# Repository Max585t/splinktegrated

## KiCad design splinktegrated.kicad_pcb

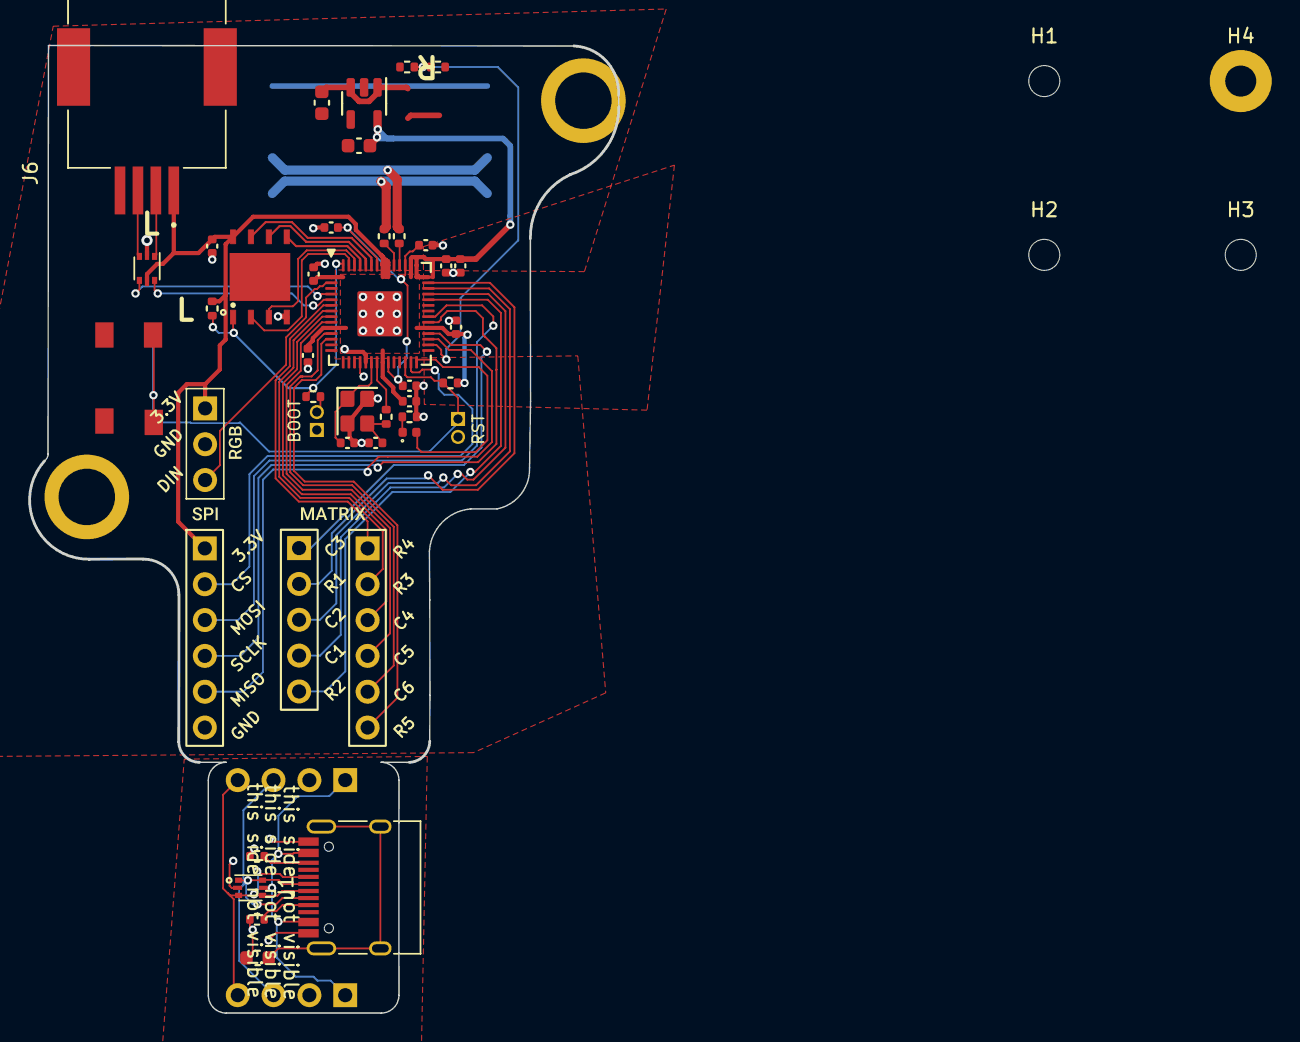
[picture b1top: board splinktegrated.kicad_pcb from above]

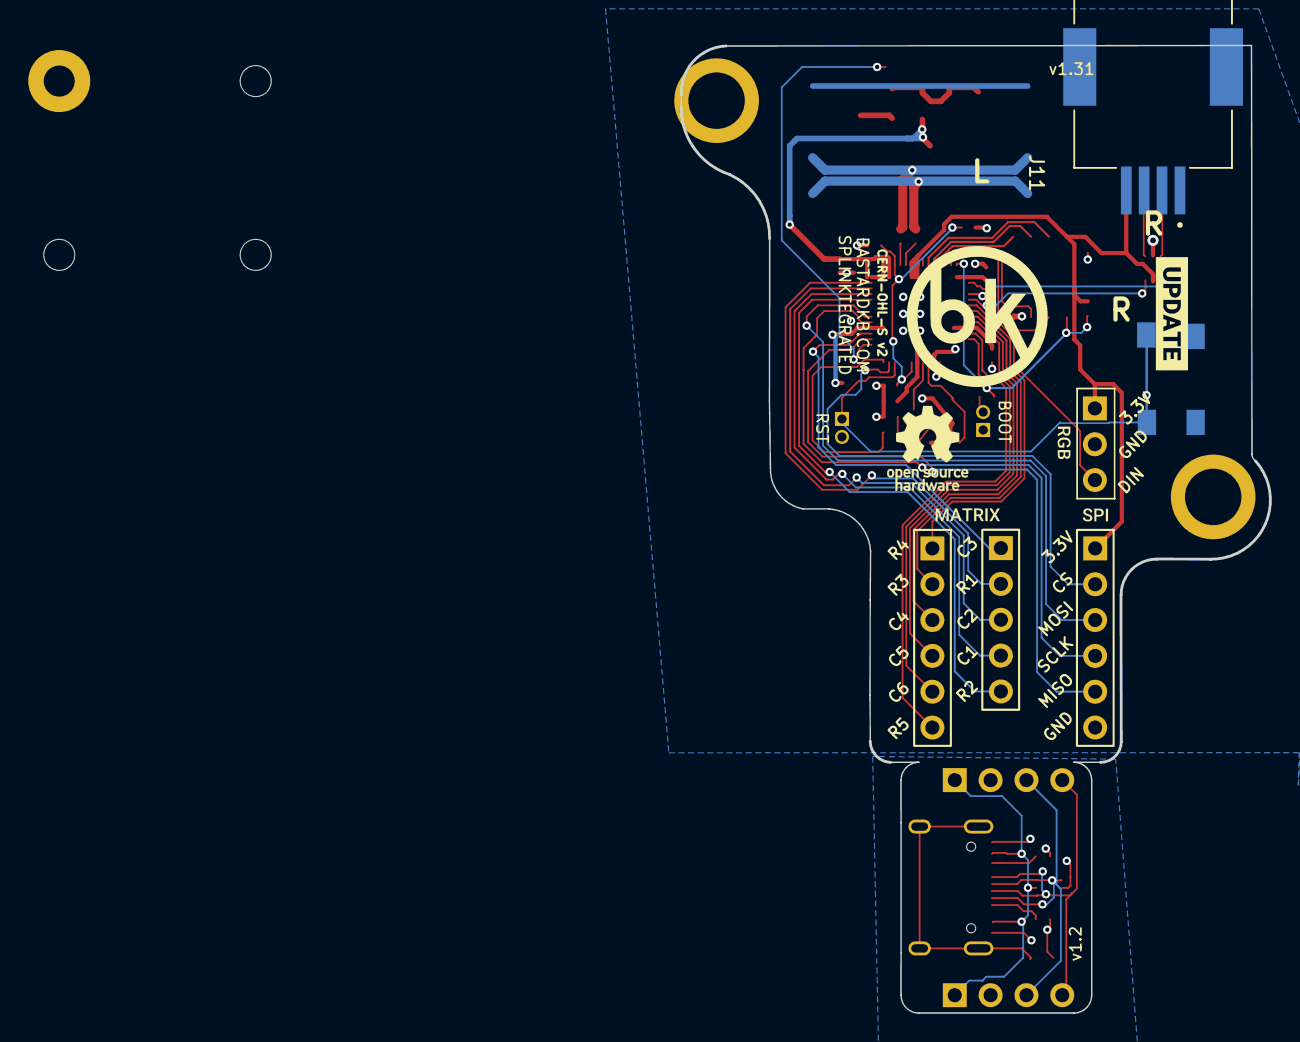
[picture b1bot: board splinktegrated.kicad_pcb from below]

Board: 2 copper layers, 41.8 x 68.6 mm, 58 parts (6 on the bottom side), 47 nets.

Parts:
C1, C2: 1µ; C_0603_1608Metric
C3, C4: 15p; C_0402_1005Metric
C5, C6: 1µ; C_0402_1005Metric
C7, C8, C9, C10, C11, C12, C13, C14: 100n; C_0402_1005Metric
D1: LED; LED_0402_1005Metric
FB1: FerriteBead_Small; L_0603_1608Metric
H1, H2, H3: MountingHole; MountingHole_2.2mm_M2
H4: MountingHole_Pad; MountingHole_2.2mm_M2_Pad
J1: USB_C_Receptacle_USB2.0; USB_C_Receptacle_HRO_TYPE-C-31-M-12
J2, J3: Conn_01x04_Female; PinHeader_1x04_P2.54mm_Vertical
J5: Conn_01x02; PinHeader_1x02_P1.27mm_Vertical
J6, J11: RJ9; AMPHENOL_73306-111LF
J7: trackball; 6_PinHeader
J8: Ribbon; 6_PinHeader
J9: RGB; header1x03
J10: Ribbon; 5_PinHeader
J13: Conn_01x02_Female; PinHeader_1x02_P1.27mm_Vertical
R1, R3, R8: 1k; R_0402_1005Metric
R2, R9, R11: 10k; R_0402_1005Metric
R4, R5, R10: 5.1k; R_0402_1005Metric
R6, R7: 27; R_0402_1005Metric
SW1, SW2: SW_SPST; PushSwitch
U1: RP2040; QFN-56-1EP_7x7mm_P0.4mm_EP3.2x3.2mm
U2, U4: USBLC6-2P6; SOT-666
U3: XC6210B332MR-G; SOT-23-5
U5: W25Q128JVS; W25Q128JVPIQ
Y1: Crystal_GND24; Crystal_SMD_2520-4Pin_2.5x2.0mm
kibuzzard-61F01C84, kibuzzard-61F01C84#2: G***; kibuzzard-61F01C84
kibuzzard-61F019CB, kibuzzard-61F019CB#2: G***; kibuzzard-61F019CB
kibuzzard-61F01940, kibuzzard-61F01940#2: G***; kibuzzard-61F01940
kibuzzard-61F01957, kibuzzard-61F01957#2: G***; kibuzzard-61F01957

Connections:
+1V1: C6.1, C7.1, C8.1, U1.23 (DVDD), U1.45 (VREG_VOUT), U1.50 (DVDD)
+3V3: C2.1, C5.1, C9.1, C10.1, C11.1, C12.1, C13.1, C14.1, J6.1, J7.1, J9.1, J11.1, R2.2, R9.2, U1.1 (IOVDD), U1.10 (IOVDD), U1.22 (IOVDD), U1.33 (IOVDD), U1.42 (IOVDD), U1.43 (ADC_AVDD), U1.44 (VREG_IN), U1.48 (USB_VDD), U1.49 (IOVDD), U2.5 (VBUS), U3.5 (VOUT), U5.8 (VCC)
+5V: C1.1, R10.2, U3.1 (VIN), U3.3 (EN)
/D+_daughter: J1.A6 (D+), J1.B6 (D+), J2.4, J3.4, U4.3 (I/O2), U4.4 (I/O2)
/D-_daughter: J1.A7 (D-), J1.B7 (D-), J2.3, J3.3, U4.1 (I/O1), U4.6 (I/O1)
/Gnd_daughter: FB1.1, J1.A1 (GND), J1.A12 (GND), J1.B1 (GND), J1.B12 (GND), J2.2, J3.2, R4.2, R5.2, U4.2 (GND)
/LED: D1.2 (A), U1.28 (GPIO17)
/QSPI_D0: U1.53 (QSPI_SD0), U5.5 (DI(IO0))
/QSPI_D1: U1.55 (QSPI_SD1), U5.2 (DO(IO1))
/QSPI_D2: U1.54 (QSPI_SD2), U5.3 (IO2)
/QSPI_D3: U1.51 (QSPI_SD3), U5.7 (IO3)
/QSPI_SCLK: U1.52 (QSPI_SCLK), U5.6 (CLK)
/QSPI_~CS: R3.2, R9.1, U1.56 (QSPI_SS), U5.1 (~CS)
/VBUS_DET: R10.1, R11.2, U1.30 (GPIO19)
/Vbus_daughter: J1.A4 (VBUS), J1.A9 (VBUS), J1.B4 (VBUS), J1.B9 (VBUS), J2.1, J3.1, U4.5 (VBUS)
/~RESET: J13.1, R2.1, SW1.1 (A), SW2.1 (A), U1.26 (RUN/~RST)
GND: C1.2, C2.2, C3.2, C4.2, C5.2, C6.2, C7.2, C8.2, C9.2, C10.2, C11.2, C12.2, C13.2, C14.2, H4.1, J5.1, J6.4, J7.6, J9.2, J11.4, J13.2, R1.1, R11.1, SW1.2 (B), SW2.2 (B), U1.19 (TESTEN), U1.57 (GND), U2.2 (GND), U3.2 (GND), U5.4 (GND), Y1.2, Y1.4
I2C1 SCL: U1.5 (GPIO3), U2.6 (I/O1)
I2C1 SCL Raw: J6.2, J11.2, U2.1 (I/O1)
I2C1 SDA: U1.4 (GPIO2), U2.4 (I/O2)
I2C1 SDA Raw: J6.3, J11.3, U2.3 (I/O2)
unnamed: C4.1, R8.1, Y1.3
unnamed: D1.1 (K), R1.2
unnamed: J1.A5 (CC1), R4.1
unnamed: J1.B5 (CC2), R5.1
unnamed: FB1.2, J1.S1 (SHIELD)
unnamed: J5.2, R3.1
unnamed: R7.2, U1.46 (USB_DM)
unnamed: R6.2, U1.47 (USB_DP)
unnamed: C3.1, U1.20 (XIN), Y1.1
unnamed: R8.2, U1.21 (XOUT)
col1_l: J10.4, U1.39 (GPIO27_ADC1)
col2_l: J10.3, U1.40 (GPIO28_ADC2)
col3_l: J10.1, U1.32 (GPIO21)
col4_l: J8.3, U1.8 (GPIO6)
col5_l: J8.4, U1.9 (GPIO7)
col6_l: J8.5, U1.11 (GPIO8)
miso_l: J7.5, U1.31 (GPIO20)
mosi_l: J7.3, U1.35 (GPIO23)
rgb_r: J9.3, U1.2 (GPIO0)
row1_l: J10.2, U1.41 (GPIO29_ADC3)
row2_l: J10.5, U1.38 (GPIO26_ADC0)
row3_l: J8.2, U1.7 (GPIO5)
row4_l: J8.1, U1.6 (GPIO4)
row5_l: J8.6, U1.12 (GPIO9)
sc_l: J7.4, U1.34 (GPIO22)
ss_l: J7.2, U1.27 (GPIO16)

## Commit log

2023-12-04 start to replace audio jacks with rj9s
2023-12-05 minor changes
2023-12-13 major work done. outline finished
2023-12-15 USB daugherboard

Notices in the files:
splinktegrated.kicad_pcb:
CERN-OHL-S v2
